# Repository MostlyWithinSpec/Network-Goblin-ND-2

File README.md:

# Network Goblin ND-2

**A Linux-powered handheld network multitool with real cable diagnostics.**

ND-2 is the bigger sibling of the [ND-1](#the-network-goblin-family) pocket cable tester. It's a custom carrier board for the Raspberry Pi Compute Module 5 with:

- a **dedicated test port** that can find opens, shorts and distance-to-fault on each pair (PHY-based TDR),
- a second gigabit port for uplink, capture and inline tapping,
- a touchscreen, battery power, 2x USB-A and HDMI out,
- a normal Linux distro underneath, so tcpdump, Wireshark, iperf3, nmap and friends just work.

Everything here, hardware and software, is open source under the MIT license.

> **Status: early hardware.** The first board, the **TDR proof dongle**, is at the fab. The full ND-2 carrier is still at the spec stage. Nothing here has been tested on real hardware yet.

---

## What's in this repo

| Path | What it is |
|---|---|
| [`docs/spec.md`](docs/spec.md) | Full ND-2 hardware spec (draft): architecture, part choices, power, BOM, risks |
| [`docs/roadmap.md`](docs/roadmap.md) | Where the project is going and in what order |
| [`docs/bring-up.md`](docs/bring-up.md) | Step-by-step first power-on and test plan for the TDR dongle |
| [`docs/ordering-jlcpcb.md`](docs/ordering-jlcpcb.md) | Exact JLCPCB settings used to order the dongle, and how to keep the cost down |
| [`hardware/tdr-dongle/`](hardware/tdr-dongle/) | **Rev A TDR proof dongle**: KiCad project, fab files, BOM, pick-and-place |
| [`hardware/nd2-carrier/`](hardware/nd2-carrier/) | The full CM5 carrier board (not started yet) |
| [`software/cabletest/`](software/cabletest/) | `nd2-cabletest`: a friendly wrapper around the Linux cable-test tools |

## The TDR proof dongle (Rev A)

A 70 x 30 mm USB 3 to gigabit Ethernet dongle that is **just the ND-2 test-port circuit**:

- **Microchip LAN7801**: USB 3 to RGMII MAC (`lan78xx` driver, mainline Linux)
- **Marvell 88E1512**: gigabit PHY with Virtual Cable Tester / TDR (`marvell` PHY driver, mainline Linux)
- **HanRun HR911130C**: 1G RJ45 magjack with LEDs
- 4-layer, 1.6 mm, all SMD parts on the top side, assembled by JLCPCB

It exists to prove that `ethtool --cable-test` works on this chip combo before building the full carrier. If it works, it's also useful by itself: **plug it into any Pi 5 or Linux laptop and you have a TDR cable tester.**

See [`hardware/tdr-dongle/README.md`](hardware/tdr-dongle/README.md) for the design details and fab files.

## Quick try (once you have a dongle)

```bash
# On a Pi 5 or any Linux machine with ethtool 5.8+ and a recent kernel
lsusb | grep 0424:7801             # the LAN7801 should show up
ip link                            # find the new interface, e.g. eth1
sudo ethtool --cable-test eth1     # per-pair OK / open / short + fault distance

# or the friendlier wrapper from this repo
sudo python3 software/cabletest/nd2-cabletest.py eth1
```

Unplug the far end of the cable first. TDR results are unreliable while there's an active link partner.

## The Network Goblin family

| Device | What it is |
|---|---|
| **ND-1** | Cheap, instant-on pocket cable tester. ESP32 + LAN8742A, 3.5" LCD. |
| **ND-2** | This repo. Linux handheld multitool on CM5, with a TDR test port. |
| **TDR dongle** | The ND-2 test port on its own, as a USB 3 dongle for any Linux box. |

## Contributing

Issues and pull requests are welcome, whether it's hardware review, bring-up results or software. See [CONTRIBUTING.md](CONTRIBUTING.md). Hardware bring-up reports on real boards are especially useful right now.

## License

[MIT](LICENSE), covering both hardware and software. Build it, fork it, sell it; a credit back to the project is appreciated.

**Not certified:** ND-2 isn't FCC/CE certified and isn't a TIA/ISO cable certifier. It tells you whether a cable is healthy enough, not whether it passes a formal certification test.

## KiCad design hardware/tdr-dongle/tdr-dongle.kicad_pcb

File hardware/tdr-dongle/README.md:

# ND-2 TDR Proof Dongle — Rev A

A small USB 3 → Gigabit Ethernet dongle that is just the ND-2 test-port circuit:
**Microchip LAN7801** (USB 3 to RGMII MAC) + **Marvell 88E1512** (GbE PHY with VCT/TDR) + HanRun 1G magjack.
Plug it into a Pi 5 / CM5 IO board and prove `ethtool --cable-test` / `--cable-test-tdr` before building the CM5 carrier.

**Status:** ERC and DRC clean, schematic/PCB parity clean, ordered from JLCPCB in Sept 2026. **Not yet tested on real hardware.** Bring-up plan: [docs/bring-up.md](../../docs/bring-up.md).

## Files

| File | What it is |
| --- | --- |
| `tdr-dongle.kicad_sch` | Schematic (KiCad 10, one A2 sheet, label-based wiring) |
| `ND2.kicad_sym` + `sym-lib-table` | Project symbols: `ND2:LAN7801`, `ND2:88E1512`, `ND2:HR911130C` |
| `ND2.pretty` + `fp-lib-table` | Project footprints (from LCSC/EasyEDA, cleaned up — see below) |
| `bom_jlcpcb.csv` | Grouped BOM in JLCPCB format (Comment, Designator, Footprint, LCSC Part #) |
| `bom.csv` | One line per part with MPN + LCSC |
| `netlist_report.txt` | Every net and the pins on it |
| `tdr-dongle.kicad_pcb` | PCB: 70 x 30 mm, 4-layer |
| `tdr-dongle.kicad_pro` | KiCad project (design rules, net classes) |
| `tdr-dongle.net` | KiCad netlist export |
| `fab/` | Fabrication package: Gerber zip, JLC BOM + CPL, layer PDF, schematic PDF, STEP, renders |
| `scripts/` | Python scripts that generated the schematic and PCB (see [scripts/README.md](scripts/README.md)) |

## Parts (LCSC, checked 2026-09-25)

| Ref | Part | LCSC | Footprint | Notes |
| --- | --- | --- | --- | --- |
| U1 | LAN7801-I/9JX | C633491 | ND2:LAN7801_QFN-64-1EP_9x9mm_P0.5mm_EP6.1mm | Only ~13 in stock at LCSC |
| U2 | 88E1512-A0-NNP2C000 | C845579 | ND2:88E1512_QFN-56-1EP_8x8mm_P0.5mm_EP4.4mm | Only ~13 in stock at LCSC |
| U3 | TLV62569DBVR | C141836 | SOT-23-5 | 3V3 buck |
| U4 | 93AA66/SN | C615340 | SOIC-8 | ORG pin (6) tied to GND = 512 x 8 |
| U5 | TPD4EUSB30DQAR | C90627 | USON-10 | USB 3 ESD |
| U6 | PRTR5V0U2X,215 | C12333 | SOT-143 | USB 2 ESD |
| J1 | HC-USB3.0-C26 (USB 3 Type-A plug, SMD) | C7501854 | ND2:USB3_A_Plug_HongCheng_HC-USB3.0-C26 | Flash-drive style plug at the board edge |
| J2 | HanRun HR911130C (1G magjack, 2 LEDs) | C50933 | ND2:RJ45_HanRun_HR911130C_Horizontal | Replaces the Pulse JK0654219NL (0 stock) |
| Y1, Y2 | X322525MOB4SI 25 MHz, CL 12 pF | C9006 | Crystal_SMD_3225-4Pin | Load caps changed to 15 pF |
| L1 | SMNR4020-2.2UH (3.4 A) | C135262 | ND2:L_4.0x4.0mm_SMNR4020 | Buck inductor |
| L2 | SMNR3015-3R3MT (1.32 A) | C135239 | ND2:L_3.0x3.0mm_SMNR3015 | LAN7801 1V2 switcher |
| FB1 | MPZ2012S601AT000 (600 Ω, 2 A) | C21519 | L_0805 | VBUS filter |
| Caps | 100 nF C1525 · 1 µF C52923 · 220 nF C16772 · 15 pF C1548 (0402) · 10 µF C15850 · 22 µF C45783 (0805) | | | |
| Resistors (0402, UNI-ROYAL) | 22R C25092 · 330R C25104 · 0R C17168 · 1.5k C25867 · 2k C4109 · 4.99k C25903 · 10k C25744 · 12k C25752 · 100k C25741 · 453k C27009 | | | |

## Changes from the first draft

- **Magjack → HanRun HR911130C.** The Pulse part had no stock. The HR911130C has one **common** center tap (pin 1 → one 100 nF to GND) and an internal Bob-Smith termination on pin 10 (tied to GND). LEDs: 11/12 green (anode/cathode), 14/13 yellow (anode/cathode).
- **EEPROM → 93AA66/SN** (the x8-only 93AA66A wasn't stocked in SOIC). ORG pin tied low selects 512 x 8.
- **Crystals → 12 pF load** (YXC, 70k in stock); load caps now 15 pF.
- **Real footprints** for U1, U2, J1, J2, L1, L2, taken from LCSC/EasyEDA and fixed up:
  - LAN7801 pads resized to Microchip's recommended land pattern (0.30 × 0.85 mm pads, 6.1 mm exposed pad), plus 5 × 5 thermal vias (0.33 mm) and a split paste stencil.
  - 88E1512 exposed pad 4.4 mm (datasheet D2/E2 = 4.37 mm), 3 × 3 thermal vias numbered to the pad, split paste.
  - HR911130C / USB plug pads renumbered to match the symbols; the RJ45 plastic posts made non-plated.

## Known issues and Rev B ideas

1. **Stock on U1 / U2** — about 13 of each at LCSC right now. Enough for a few prototypes; for more, JLCPCB global sourcing or Mouser/Digi-Key.
2. **J1 plug** hangs over the board edge and was left off the JLC assembly (hand-soldered). Rev B: USB-C receptacle + cable.
3. RGMII series resistors (22 Ω) are a starting value; tune after the first boards.
4. Optional: low-capacitance TVS on the MDI pairs, test points on RGMII/MDIO.

## Bring-up plan

1. Power only: check +5V, +3V3, LAN_1V2, LAN_2V5, PHY_1V8, PHY_1V0.
2. Plug into a Pi 5: `lsusb` should show 0424:7801. Program the EEPROM with MAC + HW_CFG (hybrid RGMII delay, CLK125_EN).
3. `dmesg` should show lan78xx attaching the Marvell 88E1510-family PHY at address 0.
4. Link test: clean 1 Gb/s link, iperf3, watch for CRC errors (wrong RGMII delay).
5. TDR: `ethtool --cable-test ethX` and `ethtool --cable-test-tdr ethX` on known cables (open, short, known lengths).

## PCB and fab package (Rev A)

- Board: 70 x 30 mm, 4-layer 1.6 mm (JLC04161H-7628). F.Cu signals, In1 = GND plane, In2 = +3V3 plane, B.Cu signals.
- Rules: 0.1 mm min track (Freerouting necks to ~0.11 at the QFN pins), 0.127 mm clearance, 0.6/0.3 mm vias.
- Routing: plane fan-out by script (scripts/fanout.py), the rest by Freerouting 2.4.1, and 2 nets fixed by hand (scripts/fix_last2.py).
- DRC: 0 errors, 0 warnings, 0 unconnected, schematic parity clean (KiCad 10.0.5).

`fab/` holds:
- `tdr-dongle_gerbers_JLC.zip`: Gerbers + Excellon drills. Upload this to JLCPCB and pick 4 layers, 1.6 mm, JLC04161H-7628.
- `tdr-dongle_BOM_JLC.csv`: the BOM (R7 is DNP and left out).
- `tdr-dongle_CPL_JLC.csv`: pick and place (89 parts, all top side, origin at the board's lower-left corner).
- `tdr-dongle_layers.pdf`, `tdr-dongle_schematic.pdf`, `tdr-dongle.step`, and top/bottom renders for review.

Caveats:
- USB3 and MDI pairs were autorouted. They are **not** length-matched or impedance-controlled. That is fine for a proof dongle but not final.
- Check part rotations in JLC's CPL preview, especially J1, J2, U1, U2 and the crystals.
- LAN7801 and 88E1512 LCSC stock was low (~13 each) when checked.

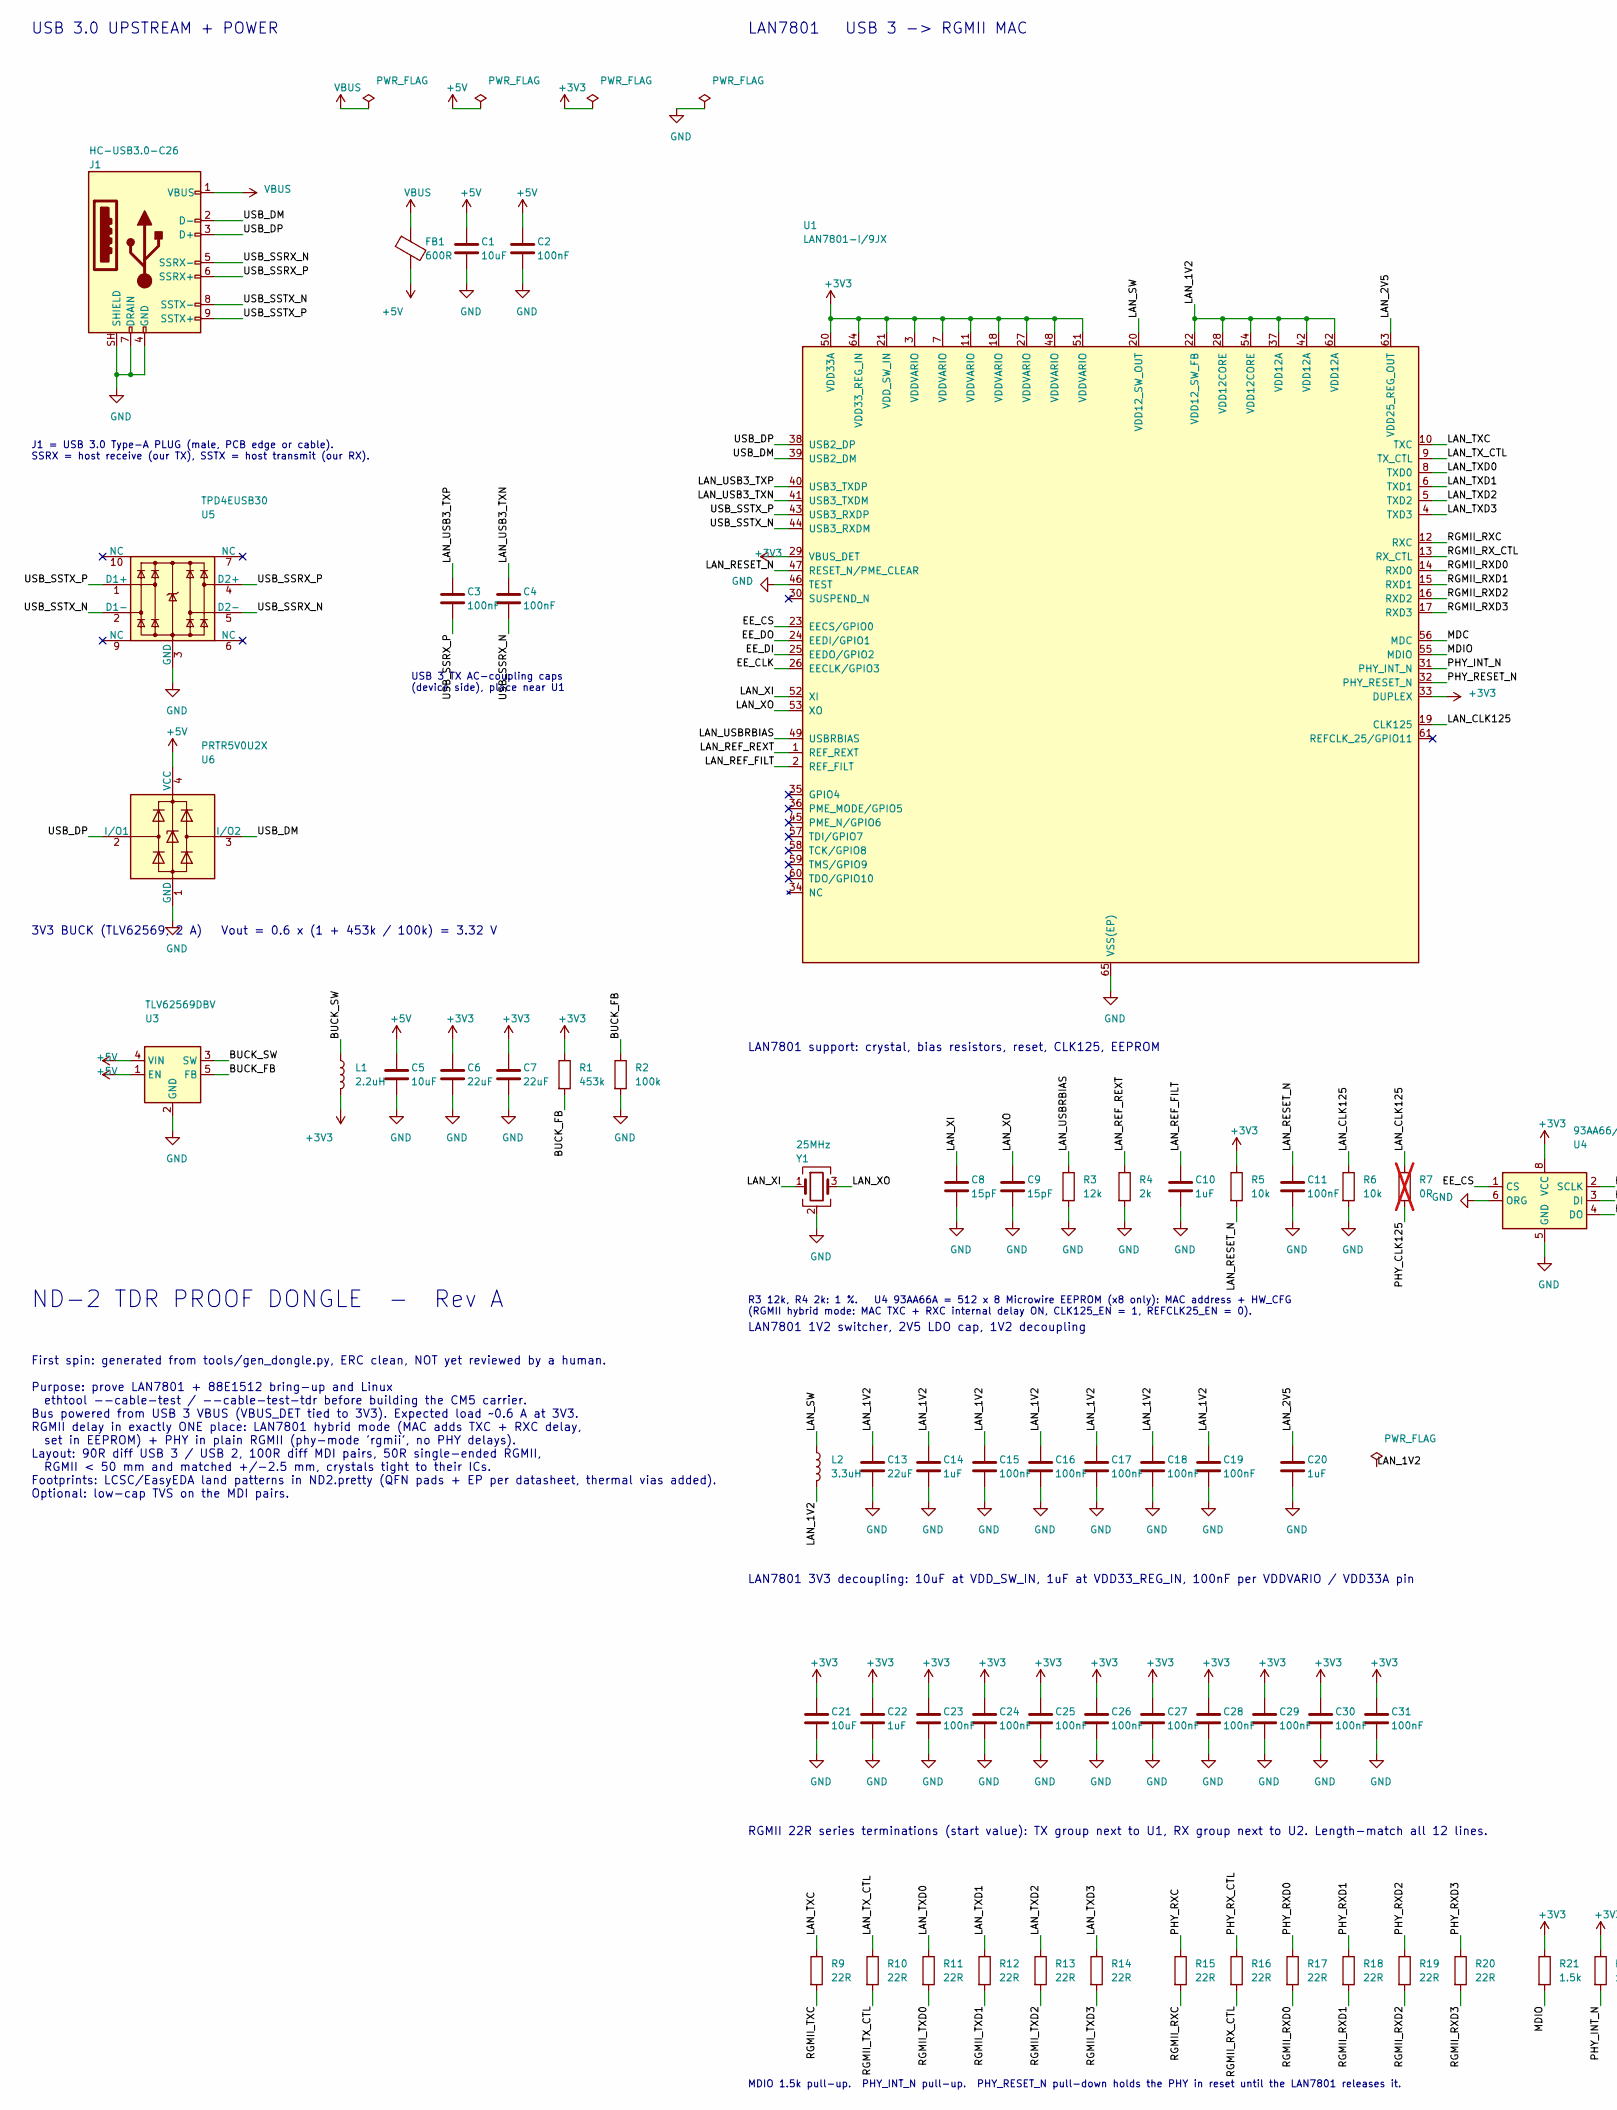
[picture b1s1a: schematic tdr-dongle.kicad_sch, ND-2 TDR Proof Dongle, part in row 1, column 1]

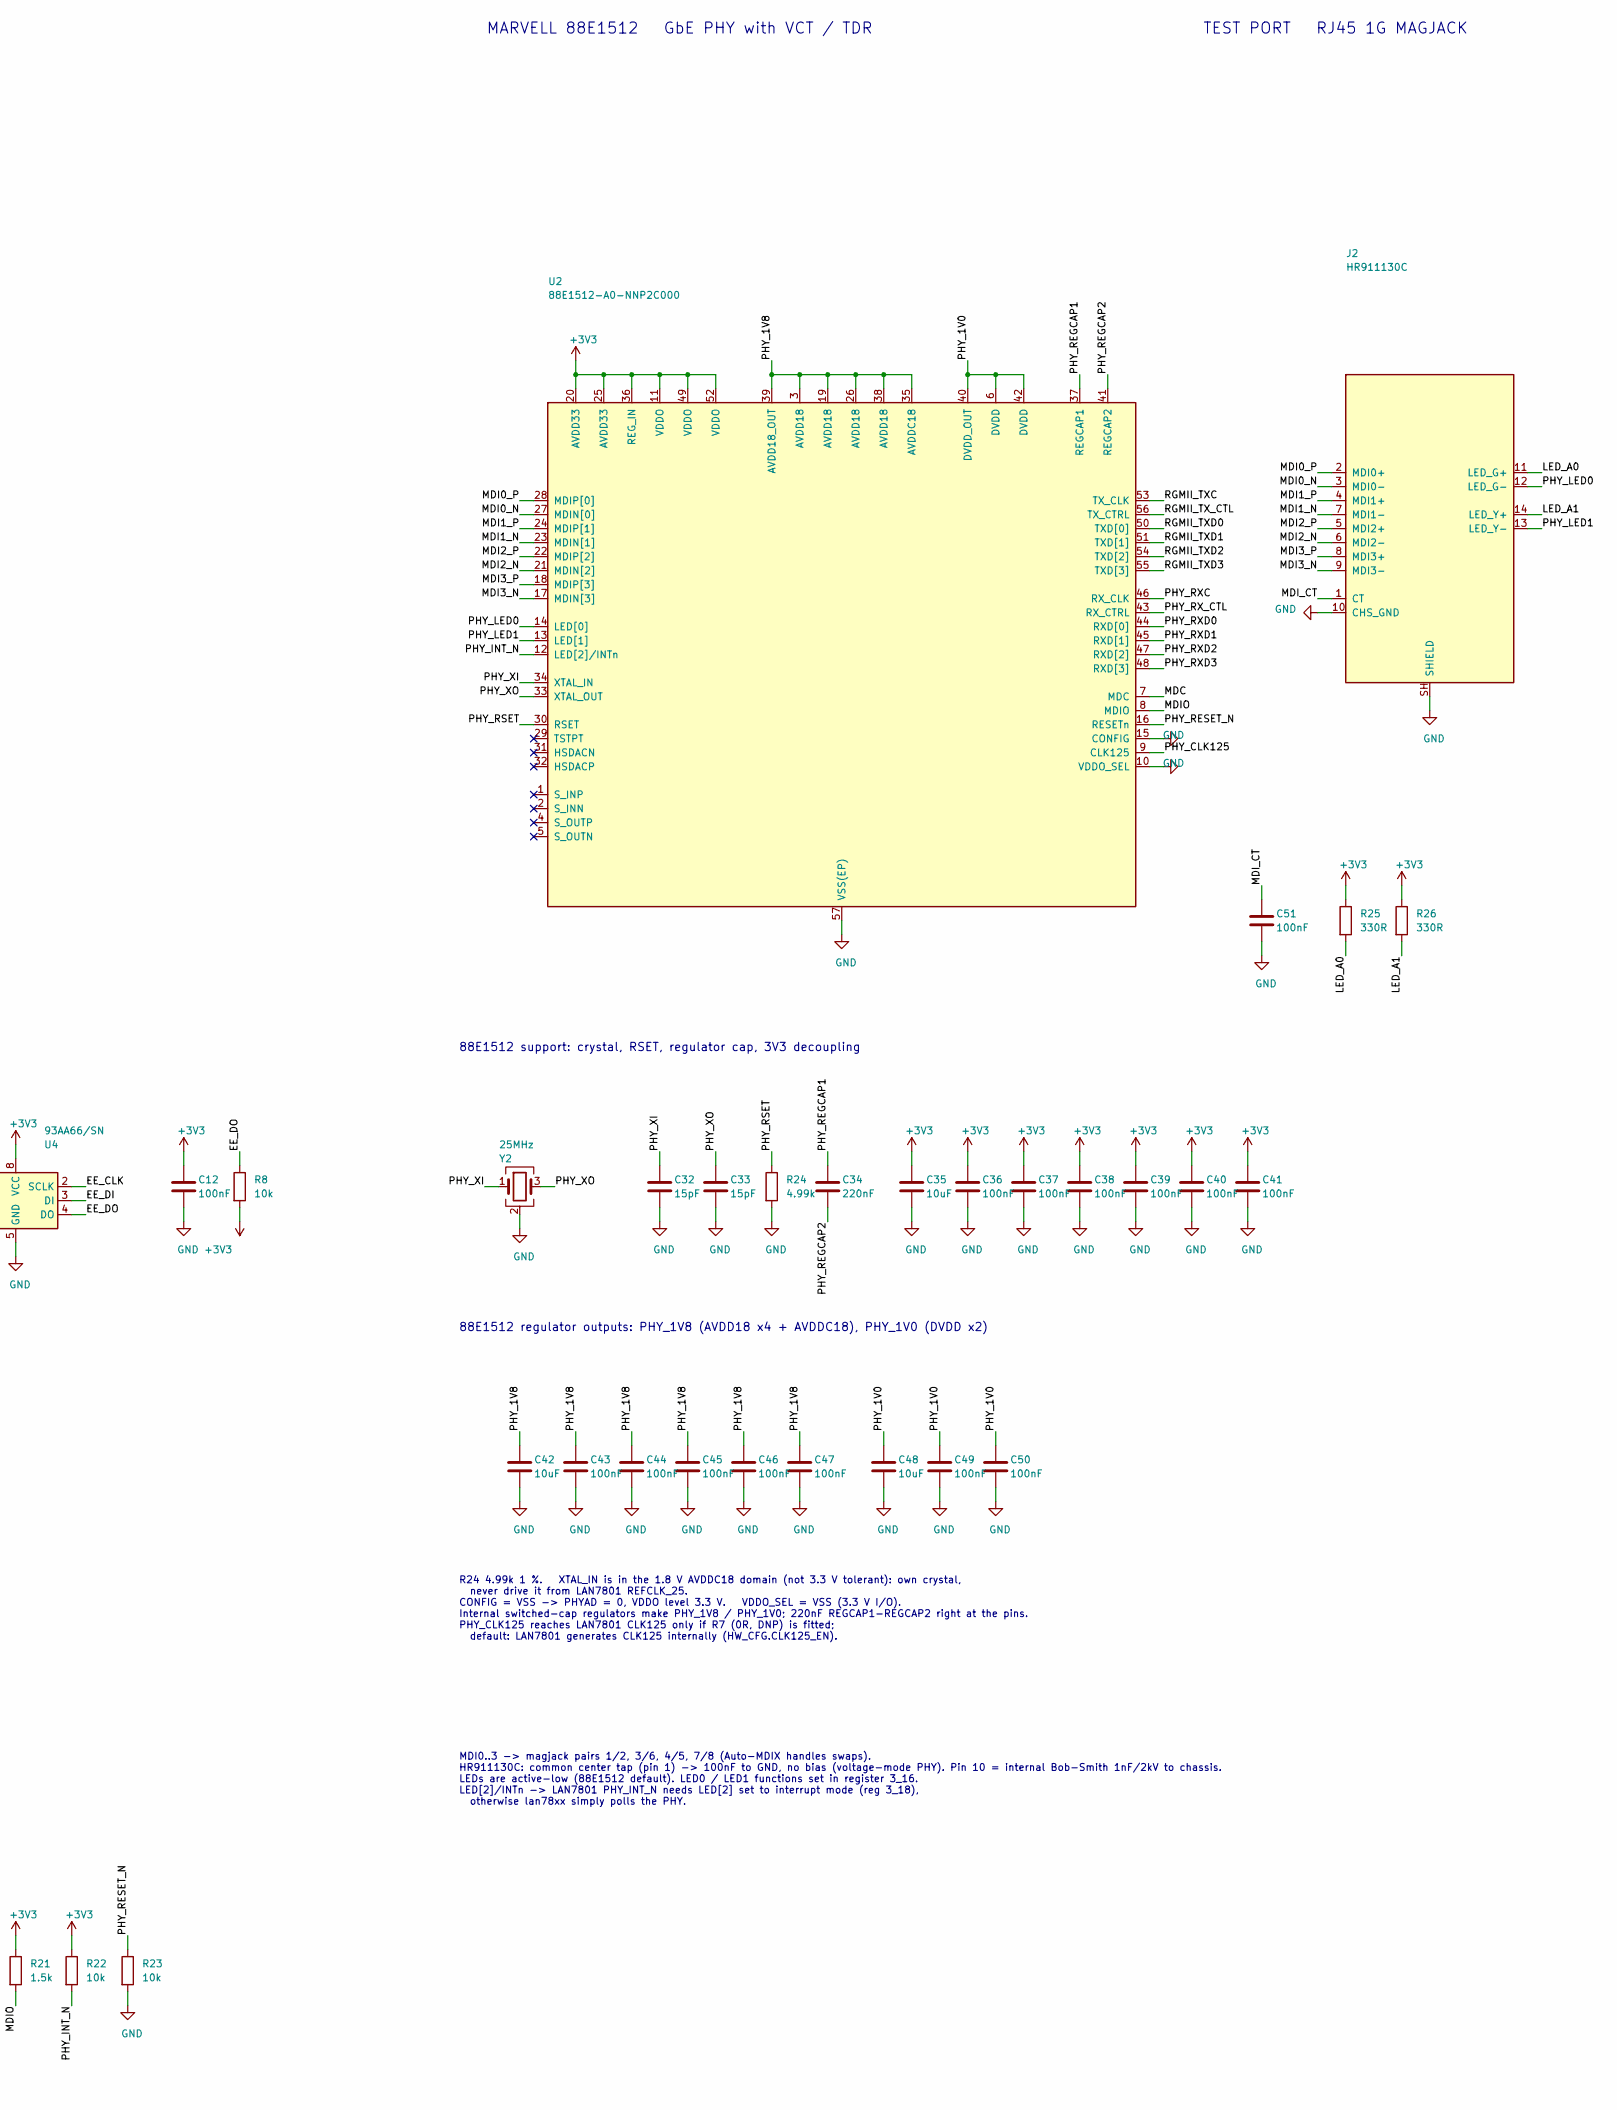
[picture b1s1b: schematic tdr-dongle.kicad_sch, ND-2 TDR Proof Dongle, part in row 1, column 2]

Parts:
C1, C5, C21, C35, C42, C48: 10uF; C_0805_2012Metric; MPN CL21A106KAYNNNE; LCSC C15850
C2, C3, C4, C11, C12, C15, C16, C17, C18, C19, C23, C24, C25, C26, C27, C28, C29, C30, C31, C36, C37, C38, C39, C40, C41, C43, C44, C45, C46, C47, C49, C50, C51: 100nF; C_0402_1005Metric; MPN CL05B104KO5NNNC; LCSC C1525
C6, C7, C13: 22uF; C_0805_2012Metric; MPN CL21A226MAQNNNE; LCSC C45783
C8, C9, C32, C33: 15pF; C_0402_1005Metric; MPN 0402CG150J500NT; LCSC C1548
C10, C14, C20, C22: 1uF; C_0402_1005Metric; MPN CL05A105KA5NQNC; LCSC C52923
C34: 220nF; C_0402_1005Metric; MPN CL05B224KO5NNNC; LCSC C16772
FB1: 600R; L_0805_2012Metric; MPN MPZ2012S601AT000; LCSC C21519
J1: HC-USB3.0-C26; USB3_A_Plug_HongCheng_HC-USB3.0-C26; MPN HC-USB3.0-C26; LCSC C7501854
J2: HR911130C; RJ45_HanRun_HR911130C_Horizontal; MPN HR911130C; LCSC C50933
L1: 2.2uH; L_4.0x4.0mm_SMNR4020; MPN SMNR4020-2.2UH; LCSC C135262
L2: 3.3uH; L_3.0x3.0mm_SMNR3015; MPN SMNR3015-3R3MT; LCSC C135239
R1: 453k; R_0402_1005Metric; MPN 0402WGF4533TCE; LCSC C27009
R2: 100k; R_0402_1005Metric; MPN 0402WGF1003TCE; LCSC C25741
R3: 12k; R_0402_1005Metric; MPN 0402WGF1202TCE; LCSC C25752
R4: 2k; R_0402_1005Metric; MPN 0402WGF2001TCE; LCSC C4109
R5, R6, R8, R22, R23: 10k; R_0402_1005Metric; MPN 0402WGF1002TCE; LCSC C25744
R7: 0R; R_0402_1005Metric; MPN 0402WGF0000TCE; LCSC C17168; not fitted
R9, R10, R11, R12, R13, R14, R15, R16, R17, R18, R19, R20: 22R; R_0402_1005Metric; MPN 0402WGF220JTCE; LCSC C25092
R21: 1.5k; R_0402_1005Metric; MPN 0402WGF1501TCE; LCSC C25867
R24: 4.99k; R_0402_1005Metric; MPN 0402WGF4991TCE; LCSC C25903
R25, R26: 330R; R_0402_1005Metric; MPN 0402WGF3300TCE; LCSC C25104
U1: LAN7801-I/9JX; LAN7801_QFN-64-1EP_9x9mm_P0.5mm_EP6.1mm; MPN LAN7801-I/9JX; LCSC C633491
U2: 88E1512-A0-NNP2C000; 88E1512_QFN-56-1EP_8x8mm_P0.5mm_EP4.4mm; MPN 88E1512-A0-NNP2C000; LCSC C845579
U3: TLV62569DBV; SOT-23-5; MPN TLV62569DBVR; LCSC C141836
U4: 93AA66/SN; SOIC-8_3.9x4.9mm_P1.27mm; MPN 93AA66/SN; LCSC C615340
U5: TPD4EUSB30; USON-10_2.5x1.0mm_P0.5mm; MPN TPD4EUSB30DQAR; LCSC C90627
U6: PRTR5V0U2X; SOT-143; MPN PRTR5V0U2X,215; LCSC C12333
Y1, Y2: 25MHz; Crystal_SMD_3225-4Pin_3.2x2.5mm; MPN X322525MOB4SI; LCSC C9006

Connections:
+3V3: C6.1, C7.1, C12.1, C21.1, C22.1, C23.1, C24.1, C25.1, C26.1, C27.1, C28.1, C29.1, C30.1, C31.1, C35.1, C36.1, C37.1, C38.1, C39.1, C40.1, C41.1, L1.2, R1.1, R5.1, R8.2, R21.1, R22.1, R25.1, R26.1, U1.3 (VDDVARIO), U1.7 (VDDVARIO), U1.11 (VDDVARIO), U1.18 (VDDVARIO), U1.21 (VDD_SW_IN), U1.27 (VDDVARIO), U1.29 (VBUS_DET), U1.33 (DUPLEX), U1.48 (VDDVARIO), U1.50 (VDD33A), U1.51 (VDDVARIO), U1.64 (VDD33_REG_IN), U2.11 (VDDO), U2.20 (AVDD33), U2.25 (AVDD33), U2.36 (REG_IN), U2.49 (VDDO), U2.52 (VDDO), U4.8 (VCC)
+5V: C1.1, C2.1, C5.1, FB1.2, U3.1 (EN), U3.4 (VIN), U6.4 (VCC)
/BUCK_FB: R1.2, R2.1, U3.5 (FB)
/BUCK_SW: L1.1, U3.3 (SW)
/EE_CLK: U1.26 (EECLK/GPIO3), U4.2 (SCLK)
/EE_CS: U1.23 (EECS/GPIO0), U4.1 (CS)
/EE_DI: U1.25 (EEDO/GPIO2), U4.3 (DI)
/EE_DO: R8.1, U1.24 (EEDI/GPIO1), U4.4 (DO)
/LAN_1V2: C13.1, C14.1, C15.1, C16.1, C17.1, C18.1, C19.1, L2.2, U1.22 (VDD12_SW_FB), U1.28 (VDD12CORE), U1.37 (VDD12A), U1.42 (VDD12A), U1.54 (VDD12CORE), U1.62 (VDD12A)
/LAN_2V5: C20.1, U1.63 (VDD25_REG_OUT)
/LAN_CLK125: R6.1, R7.1, U1.19 (CLK125)
/LAN_REF_FILT: C10.1, U1.2 (REF_FILT)
/LAN_REF_REXT: R4.1, U1.1 (REF_REXT)
/LAN_RESET_N: C11.1, R5.2, U1.47 (RESET_N/PME_CLEAR)
/LAN_SW: L2.1, U1.20 (VDD12_SW_OUT)
/LAN_TXC: R9.1, U1.10 (TXC)
/LAN_TXD0: R11.1, U1.8 (TXD0)
/LAN_TXD1: R12.1, U1.6 (TXD1)
/LAN_TXD2: R13.1, U1.5 (TXD2)
/LAN_TXD3: R14.1, U1.4 (TXD3)
/LAN_TX_CTL: R10.1, U1.9 (TX_CTL)
/LAN_USB3_TXN: C4.1, U1.41 (USB3_TXDM)
/LAN_USB3_TXP: C3.1, U1.40 (USB3_TXDP)
/LAN_USBRBIAS: R3.1, U1.49 (USBRBIAS)
/LAN_XI: C8.1, U1.52 (XI), Y1.1
/LAN_XO: C9.1, U1.53 (XO), Y1.3
/LED_A0: J2.11 (LED_G+), R25.2
/LED_A1: J2.14 (LED_Y+), R26.2
/MDC: U1.56 (MDC), U2.7 (MDC)
/MDI0_N: J2.3 (MDI0-), U2.27 (MDIN[0])
/MDI0_P: J2.2 (MDI0+), U2.28 (MDIP[0])
/MDI1_N: J2.7 (MDI1-), U2.23 (MDIN[1])
/MDI1_P: J2.4 (MDI1+), U2.24 (MDIP[1])
/MDI2_N: J2.6 (MDI2-), U2.21 (MDIN[2])
/MDI2_P: J2.5 (MDI2+), U2.22 (MDIP[2])
/MDI3_N: J2.9 (MDI3-), U2.17 (MDIN[3])
/MDI3_P: J2.8 (MDI3+), U2.18 (MDIP[3])
/MDIO: R21.2, U1.55 (MDIO), U2.8 (MDIO)
/MDI_CT: C51.1, J2.1 (CT)
/PHY_1V0: C48.1, C49.1, C50.1, U2.6 (DVDD), U2.40 (DVDD_OUT), U2.42 (DVDD)
/PHY_1V8: C42.1, C43.1, C44.1, C45.1, C46.1, C47.1, U2.3 (AVDD18), U2.19 (AVDD18), U2.26 (AVDD18), U2.35 (AVDDC18), U2.38 (AVDD18), U2.39 (AVDD18_OUT)
/PHY_CLK125: R7.2, U2.9 (CLK125)
/PHY_INT_N: R22.2, U1.31 (PHY_INT_N), U2.12 (LED[2]/INTn)
/PHY_LED0: J2.12 (LED_G-), U2.14 (LED[0])
/PHY_LED1: J2.13 (LED_Y-), U2.13 (LED[1])
/PHY_REGCAP1: C34.1, U2.37 (REGCAP1)
/PHY_REGCAP2: C34.2, U2.41 (REGCAP2)
/PHY_RESET_N: R23.1, U1.32 (PHY_RESET_N), U2.16 (RESETn)
/PHY_RSET: R24.1, U2.30 (RSET)
/PHY_RXC: R15.1, U2.46 (RX_CLK)
/PHY_RXD0: R17.1, U2.44 (RXD[0])
/PHY_RXD1: R18.1, U2.45 (RXD[1])
/PHY_RXD2: R19.1, U2.47 (RXD[2])
/PHY_RXD3: R20.1, U2.48 (RXD[3])
/PHY_RX_CTL: R16.1, U2.43 (RX_CTRL)
/PHY_XI: C32.1, U2.34 (XTAL_IN), Y2.1
/PHY_XO: C33.1, U2.33 (XTAL_OUT), Y2.3
/RGMII_RXC: R15.2, U1.12 (RXC)
/RGMII_RXD0: R17.2, U1.14 (RXD0)
/RGMII_RXD1: R18.2, U1.15 (RXD1)
/RGMII_RXD2: R19.2, U1.16 (RXD2)
/RGMII_RXD3: R20.2, U1.17 (RXD3)
/RGMII_RX_CTL: R16.2, U1.13 (RX_CTL)
/RGMII_TXC: R9.2, U2.53 (TX_CLK)
/RGMII_TXD0: R11.2, U2.50 (TXD[0])
/RGMII_TXD1: R12.2, U2.51 (TXD[1])
/RGMII_TXD2: R13.2, U2.54 (TXD[2])
/RGMII_TXD3: R14.2, U2.55 (TXD[3])
/RGMII_TX_CTL: R10.2, U2.56 (TX_CTRL)
/USB_DM: J1.2 (D-), U1.39 (USB2_DM), U6.3 (I/O2)
/USB_DP: J1.3 (D+), U1.38 (USB2_DP), U6.2 (I/O1)
/USB_SSRX_N: C4.2, J1.5 (SSRX-), U5.5 (D2-)
/USB_SSRX_P: C3.2, J1.6 (SSRX+), U5.4 (D2+)
/USB_SSTX_N: J1.8 (SSTX-), U1.44 (USB3_RXDM), U5.2 (D1-)
/USB_SSTX_P: J1.9 (SSTX+), U1.43 (USB3_RXDP), U5.1 (D1+)
GND: C1.2, C2.2, C5.2, C6.2, C7.2, C8.2, C9.2, C10.2, C11.2, C12.2, C13.2, C14.2, C15.2, C16.2, C17.2, C18.2, C19.2, C20.2, C21.2, C22.2, C23.2, C24.2, C25.2, C26.2, C27.2, C28.2, C29.2, C30.2, C31.2, C32.2, C33.2, C35.2, C36.2, C37.2, C38.2, C39.2, C40.2, C41.2, C42.2, C43.2, C44.2, C45.2, C46.2, C47.2, C48.2, C49.2, C50.2, C51.2, J1.4 (GND), J1.7 (DRAIN), J1.SH (SHIELD), J2.10 (CHS_GND), J2.SH (SHIELD), R2.2, R3.2, R4.2, R6.2, R23.2, R24.2, U1.46 (TEST), U1.65 (VSS(EP)), U2.10 (VDDO_SEL), U2.15 (CONFIG), U2.57 (VSS(EP)), U3.2 (GND), U4.5 (GND), U4.6 (ORG), U5.3 (GND), U5.8 (GND), U6.1 (GND), Y1.2 (G), Y1.4 (G), Y2.2 (G), Y2.4 (G)
VBUS: FB1.1, J1.1 (VBUS)

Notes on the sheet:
USB 3.0 UPSTREAM + POWER
J1 = USB 3.0 Type-A PLUG (male, PCB edge or cable). SSRX = host receive (our TX), SSTX = host transmit (our RX).
USB 3 TX AC-coupling caps (device side), place near U1
3V3 BUCK (TLV62569, 2 A) Vout = 0.6 x (1 + 453k / 100k) = 3.32 V
LAN7801 USB 3 -> RGMII MAC
LAN7801 support: crystal, bias resistors, reset, CLK125, EEPROM
R3 12k, R4 2k: 1 %. U4 93AA66A = 512 x 8 Microwire EEPROM (x8 only): MAC address + HW_CFG (RGMII hybrid mode: MAC TXC + RXC internal delay ON, CLK125_EN = 1, REFCLK25_EN = 0).
LAN7801 1V2 switcher, 2V5 LDO cap, 1V2 decoupling
LAN7801 3V3 decoupling: 10uF at VDD_SW_IN, 1uF at VDD33_REG_IN, 100nF per VDDVARIO / VDD33A pin
RGMII 22R series terminations (start value): TX group next to U1, RX group next to U2. Length-match all 12 lines.
MDIO 1.5k pull-up. PHY_INT_N pull-up. PHY_RESET_N pull-down holds the PHY in reset until the LAN7801 releases it.
MARVELL 88E1512 GbE PHY with VCT / TDR
88E1512 support: crystal, RSET, regulator cap, 3V3 decoupling
88E1512 regulator outputs: PHY_1V8 (AVDD18 x4 + AVDDC18), PHY_1V0 (DVDD x2)
R24 4.99k 1 %. XTAL_IN is in the 1.8 V AVDDC18 domain (not 3.3 V tolerant): own crystal, never drive it from LAN7801 REFCLK_25. CONFIG = VSS -> PHYAD = 0, VDDO level 3.3 V. VDDO_SEL = VSS (3.3 V I/O). Internal switched-cap regulators make PHY_1V8 / PHY_1V0; 220nF REGCAP1-REGCAP2 right at the pins. 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
MDI0..3 -> magjack pairs 1/2, 3/6, 4/5, 7/8 (Auto-MDIX handles swaps). HR911130C: common center tap (pin 1) -> 100nF to GND, no bias (voltage-mode PHY). Pin 10 = internal Bob-Smith 1nF/2kV to chassis. LEDs are active-low (88E1512 default). LED0 / LED1 functions set in register 3_16. LED[2]/INTn -> 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
TEST PORT RJ45 1G MAGJACK
ND-2 TDR PROOF DONGLE - Rev A
First spin: generated from tools/gen_dongle.py, ERC clean, NOT yet reviewed by a human. Purpose: prove LAN7801 + 88E1512 bring-up and Linux ethtool --cable-test / --cable-test-tdr before building the CM5 carrier. Bus powered from USB 3 VBUS (VBUS_DET tied to 3V3). Expected load ~0.6 A at 3V3. RGMII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

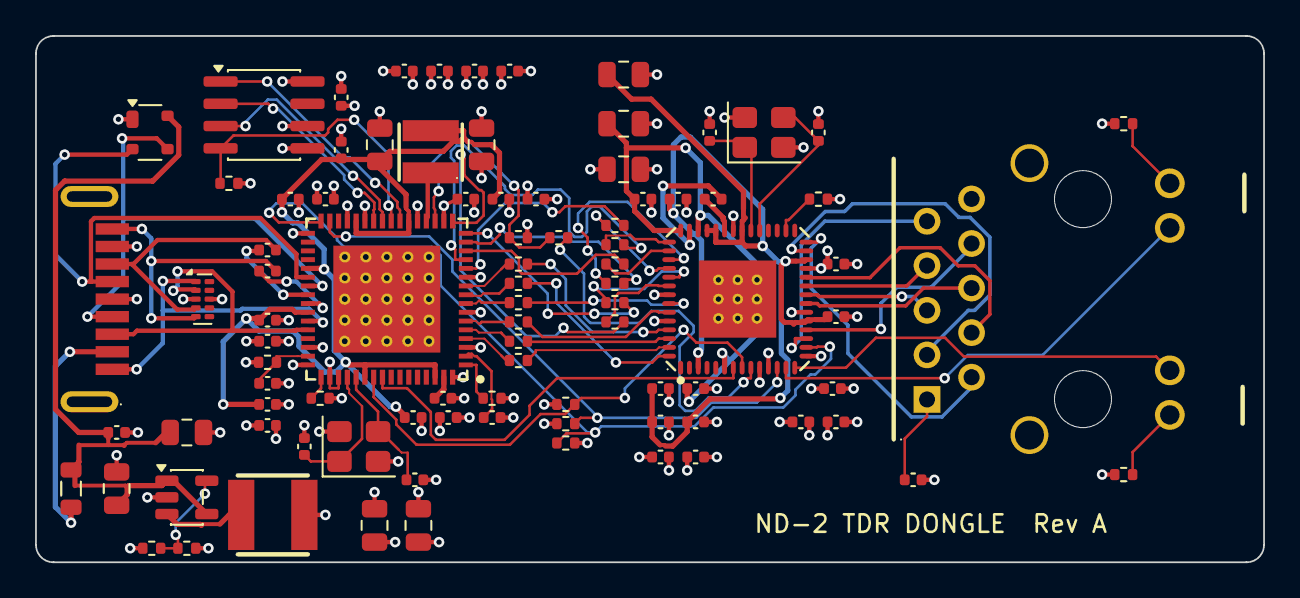
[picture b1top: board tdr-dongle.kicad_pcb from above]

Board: 4 copper layers, 70.0 x 30.0 mm, 90 parts (0 on the bottom side), 77 nets.

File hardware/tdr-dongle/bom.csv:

Ref,Value,Footprint,DNP,MPN,LCSC
C1,"10uF",Capacitor_SMD:C_0805_2012Metric,,"CL21A106KAYNNNE",C15850
C2,"100nF",Capacitor_SMD:C_0402_1005Metric,,"CL05B104KO5NNNC",C1525
C3,"100nF",Capacitor_SMD:C_0402_1005Metric,,"CL05B104KO5NNNC",C1525
C4,"100nF",Capacitor_SMD:C_0402_1005Metric,,"CL05B104KO5NNNC",C1525
C5,"10uF",Capacitor_SMD:C_0805_2012Metric,,"CL21A106KAYNNNE",C15850
C6,"22uF",Capacitor_SMD:C_0805_2012Metric,,"CL21A226MAQNNNE",C45783
C7,"22uF",Capacitor_SMD:C_0805_2012Metric,,"CL21A226MAQNNNE",C45783
C8,"15pF",Capacitor_SMD:C_0402_1005Metric,,"0402CG150J500NT",C1548
C9,"15pF",Capacitor_SMD:C_0402_1005Metric,,"0402CG150J500NT",C1548
C10,"1uF",Capacitor_SMD:C_0402_1005Metric,,"CL05A105KA5NQNC",C52923
C11,"100nF",Capacitor_SMD:C_0402_1005Metric,,"CL05B104KO5NNNC",C1525
C12,"100nF",Capacitor_SMD:C_0402_1005Metric,,"CL05B104KO5NNNC",C1525
C13,"22uF",Capacitor_SMD:C_0805_2012Metric,,"CL21A226MAQNNNE",C45783
C14,"1uF",Capacitor_SMD:C_0402_1005Metric,,"CL05A105KA5NQNC",C52923
C15,"100nF",Capacitor_SMD:C_0402_1005Metric,,"CL05B104KO5NNNC",C1525
C16,"100nF",Capacitor_SMD:C_0402_1005Metric,,"CL05B104KO5NNNC",C1525
C17,"100nF",Capacitor_SMD:C_0402_1005Metric,,"CL05B104KO5NNNC",C1525
C18,"100nF",Capacitor_SMD:C_0402_1005Metric,,"CL05B104KO5NNNC",C1525
C19,"100nF",Capacitor_SMD:C_0402_1005Metric,,"CL05B104KO5NNNC",C1525
C20,"1uF",Capacitor_SMD:C_0402_1005Metric,,"CL05A105KA5NQNC",C52923
C21,"10uF",Capacitor_SMD:C_0805_2012Metric,,"CL21A106KAYNNNE",C15850
C22,"1uF",Capacitor_SMD:C_0402_1005Metric,,"CL05A105KA5NQNC",C52923
C23,"100nF",Capacitor_SMD:C_0402_1005Metric,,"CL05B104KO5NNNC",C1525
C24,"100nF",Capacitor_SMD:C_0402_1005Metric,,"CL05B104KO5NNNC",C1525
C25,"100nF",Capacitor_SMD:C_0402_1005Metric,,"CL05B104KO5NNNC",C1525
C26,"100nF",Capacitor_SMD:C_0402_1005Metric,,"CL05B104KO5NNNC",C1525
C27,"100nF",Capacitor_SMD:C_0402_1005Metric,,"CL05B104KO5NNNC",C1525
C28,"100nF",Capacitor_SMD:C_0402_1005Metric,,"CL05B104KO5NNNC",C1525
C29,"100nF",Capacitor_SMD:C_0402_1005Metric,,"CL05B104KO5NNNC",C1525
C30,"100nF",Capacitor_SMD:C_0402_1005Metric,,"CL05B104KO5NNNC",C1525
C31,"100nF",Capacitor_SMD:C_0402_1005Metric,,"CL05B104KO5NNNC",C1525
C32,"15pF",Capacitor_SMD:C_0402_1005Metric,,"0402CG150J500NT",C1548
C33,"15pF",Capacitor_SMD:C_0402_1005Metric,,"0402CG150J500NT",C1548
C34,"220nF",Capacitor_SMD:C_0402_1005Metric,,"CL05B224KO5NNNC",C16772
C35,"10uF",Capacitor_SMD:C_0805_2012Metric,,"CL21A106KAYNNNE",C15850
C36,"100nF",Capacitor_SMD:C_0402_1005Metric,,"CL05B104KO5NNNC",C1525
C37,"100nF",Capacitor_SMD:C_0402_1005Metric,,"CL05B104KO5NNNC",C1525
C38,"100nF",Capacitor_SMD:C_0402_1005Metric,,"CL05B104KO5NNNC",C1525
C39,"100nF",Capacitor_SMD:C_0402_1005Metric,,"CL05B104KO5NNNC",C1525
C40,"100nF",Capacitor_SMD:C_0402_1005Metric,,"CL05B104KO5NNNC",C1525
C41,"100nF",Capacitor_SMD:C_0402_1005Metric,,"CL05B104KO5NNNC",C1525
C42,"10uF",Capacitor_SMD:C_0805_2012Metric,,"CL21A106KAYNNNE",C15850
C43,"100nF",Capacitor_SMD:C_0402_1005Metric,,"CL05B104KO5NNNC",C1525
C44,"100nF",Capacitor_SMD:C_0402_1005Metric,,"CL05B104KO5NNNC",C1525
C45,"100nF",Capacitor_SMD:C_0402_1005Metric,,"CL05B104KO5NNNC",C1525
C46,"100nF",Capacitor_SMD:C_0402_1005Metric,,"CL05B104KO5NNNC",C1525
C47,"100nF",Capacitor_SMD:C_0402_1005Metric,,"CL05B104KO5NNNC",C1525
C48,"10uF",Capacitor_SMD:C_0805_2012Metric,,"CL21A106KAYNNNE",C15850
C49,"100nF",Capacitor_SMD:C_0402_1005Metric,,"CL05B104KO5NNNC",C1525
C50,"100nF",Capacitor_SMD:C_0402_1005Metric,,"CL05B104KO5NNNC",C1525
C51,"100nF",Capacitor_SMD:C_0402_1005Metric,,"CL05B104KO5NNNC",C1525
FB1,"600R",Inductor_SMD:L_0805_2012Metric,,"MPZ2012S601AT000",C21519
J1,"HC-USB3.0-C26",ND2:USB3_A_Plug_HongCheng_HC-USB3.0-C26,,"HC-USB3.0-C26",C7501854
J2,"HR911130C",ND2:RJ45_HanRun_HR911130C_Horizontal,,"HR911130C",C50933
L1,"2.2uH",ND2:L_4.0x4.0mm_SMNR4020,,"SMNR4020-2.2UH",C135262
L2,"3.3uH",ND2:L_3.0x3.0mm_SMNR3015,,"SMNR3015-3R3MT",C135239
R1,"453k",Resistor_SMD:R_0402_1005Metric,,"0402WGF4533TCE",C27009
R2,"100k",Resistor_SMD:R_0402_1005Metric,,"0402WGF1003TCE",C25741
R3,"12k",Resistor_SMD:R_0402_1005Metric,,"0402WGF1202TCE",C25752
R4,"2k",Resistor_SMD:R_0402_1005Metric,,"0402WGF2001TCE",C4109
R5,"10k",Resistor_SMD:R_0402_1005Metric,,"0402WGF1002TCE",C25744
R6,"10k",Resistor_SMD:R_0402_1005Metric,,"0402WGF1002TCE",C25744
R7,"0R",Resistor_SMD:R_0402_1005Metric,DNP,"0402WGF0000TCE",C17168
R8,"10k",Resistor_SMD:R_0402_1005Metric,,"0402WGF1002TCE",C25744
R9,"22R",Resistor_SMD:R_0402_1005Metric,,"0402WGF220JTCE",C25092
R10,"22R",Resistor_SMD:R_0402_1005Metric,,"0402WGF220JTCE",C25092
R11,"22R",Resistor_SMD:R_0402_1005Metric,,"0402WGF220JTCE",C25092
R12,"22R",Resistor_SMD:R_0402_1005Metric,,"0402WGF220JTCE",C25092
R13,"22R",Resistor_SMD:R_0402_1005Metric,,"0402WGF220JTCE",C25092
R14,"22R",Resistor_SMD:R_0402_1005Metric,,"0402WGF220JTCE",C25092
R15,"22R",Resistor_SMD:R_0402_1005Metric,,"0402WGF220JTCE",C25092
R16,"22R",Resistor_SMD:R_0402_1005Metric,,"0402WGF220JTCE",C25092
R17,"22R",Resistor_SMD:R_0402_1005Metric,,"0402WGF220JTCE",C25092
R18,"22R",Resistor_SMD:R_0402_1005Metric,,"0402WGF220JTCE",C25092
R19,"22R",Resistor_SMD:R_0402_1005Metric,,"0402WGF220JTCE",C25092
R20,"22R",Resistor_SMD:R_0402_1005Metric,,"0402WGF220JTCE",C25092
R21,"1.5k",Resistor_SMD:R_0402_1005Metric,,"0402WGF1501TCE",C25867
R22,"10k",Resistor_SMD:R_0402_1005Metric,,"0402WGF1002TCE",C25744
R23,"10k",Resistor_SMD:R_0402_1005Metric,,"0402WGF1002TCE",C25744
R24,"4.99k",Resistor_SMD:R_0402_1005Metric,,"0402WGF4991TCE",C25903
R25,"330R",Resistor_SMD:R_0402_1005Metric,,"0402WGF3300TCE",C25104
R26,"330R",Resistor_SMD:R_0402_1005Metric,,"0402WGF3300TCE",C25104
U1,"LAN7801-I/9JX",ND2:LAN7801_QFN-64-1EP_9x9mm_P0.5mm_EP6.1mm,,"LAN7801-I/9JX",C633491
U2,"88E1512-A0-NNP2C000",ND2:88E1512_QFN-56-1EP_8x8mm_P0.5mm_EP4.4mm,,"88E1512-A0-NNP2C000",C845579
U3,"TLV62569DBV",Package_TO_SOT_SMD:SOT-23-5,,"TLV62569DBVR",C141836
U4,"93AA66/SN",Package_SO:SOIC-8_3.9x4.9mm_P1.27mm,,"93AA66/SN",C615340
U5,"TPD4EUSB30",Package_SON:USON-10_2.5x1.0mm_P0.5mm,,"TPD4EUSB30DQAR",C90627
U6,"PRTR5V0U2X",Package_TO_SOT_SMD:SOT-143,,"PRTR5V0U2X,215",C12333
Y1,"25MHz",Crystal:Crystal_SMD_3225-4Pin_3.2x2.5mm,,"X322525MOB4SI",C9006
Y2,"25MHz",Crystal:Crystal_SMD_3225-4Pin_3.2x2.5mm,,"X322525MOB4SI",C9006

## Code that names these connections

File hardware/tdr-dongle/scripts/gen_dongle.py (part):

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LAN_LEFT = [P(38, 'USB2_DP', 'bidirectional'), P(39, 'USB2_DM', 'bidirectional'), None,
            P(40, 'USB3_TXDP', 'output'), P(41, 'USB3_TXDM', 'output'), P(43, 'USB3_RXDP', 'input'), P(44, 'USB3_RXDM', 'input'), None,
            P(29, 'VBUS_DET', 'input'), P(47, 'RESET_N/PME_CLEAR', 'input'), P(46, 'TEST', 'input'), P(30, 'SUSPEND_N', 'output'), None,
            P(23, 'EECS/GPIO0', 'output'), P(24, 'EEDI/GPIO1', 'input'), P(25, 'EEDO/GPIO2', 'output'), P(26, 'EECLK/GPIO3', 'output'), None,
            P(52, 'XI', 'input'), P(53, 'XO', 'output'), None,
            P(49, 'USBRBIAS', 'passive'), P(1, 'REF_REXT', 'passive'), P(2, 'REF_FILT', 'passive'), None,
            P(35, 'GPIO4', 'bidirectional'), P(36, 'PME_MODE/GPIO5', 'bidirectional'), P(45, 'PME_N/GPIO6', 'bidirectional'),
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    C('100nF', 'LAN_1V2', 'GND', *r())
C('1uF', 'LAN_2V5', 'GND', *r(5.08))
fx, fy = r(5.08)
pwr_flag(fx, fy); label('LAN_1V2', fx, fy, 'R')

Y1b = Y1 + 45.72
text('LAN7801 3V3 decoupling: 10uF at VDD_SW_IN, 1uF at VDD33_REG_IN, 100nF per VDDVARIO / VDD33A pin', 150, Y1b - 26, 1.5)
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text('R24 4.99k 1 %.   XTAL_IN is in the 1.8 V AVDDC18 domain (not 3.3 V tolerant): own crystal,'
     '\n  never drive it from LAN7801 REFCLK_25.'
     '\nCONFIG = VSS -> PHYAD = 0, VDDO level 3.3 V.   VDDO_SEL = VSS (3.3 V I/O).'
     '\nInternal switched-cap regulators make PHY_1V8 / PHY_1V0; 220nF REGCAP1-REGCAP2 right at the pins.'
     '\nPHY_CLK125 reaches LAN7801 CLK125 only if R7 (0R, DNP) is fitted;'
     '\n  default: LAN7801 generates CLK125 internally (HW_CFG.CLK125_EN).', 375, Y3 + 20)
text('MDI0..3 -> magjack pairs 1/2, 3/6, 4/5, 7/8 (Auto-MDIX handles swaps).'
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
